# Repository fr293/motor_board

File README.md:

# stepper motor control board

This motor control board is designed to work with the [Open Flexure microscope](https://github.com/rwb27/openflexure_microscope) and connect to a Raspberry Pi.  It is based around three parallel ATTiny 841 microcontrollers running the Arduino Firmware through SpenceKonde's [ATTinyCore](https://github.com/SpenceKonde/ATTinyCore). 

Each ATTiny 841 controls a ULN2003 Darlington transistor array operating at 5V, running a 28BYJ-48 stepper motor with a 64:1 gear ratio.

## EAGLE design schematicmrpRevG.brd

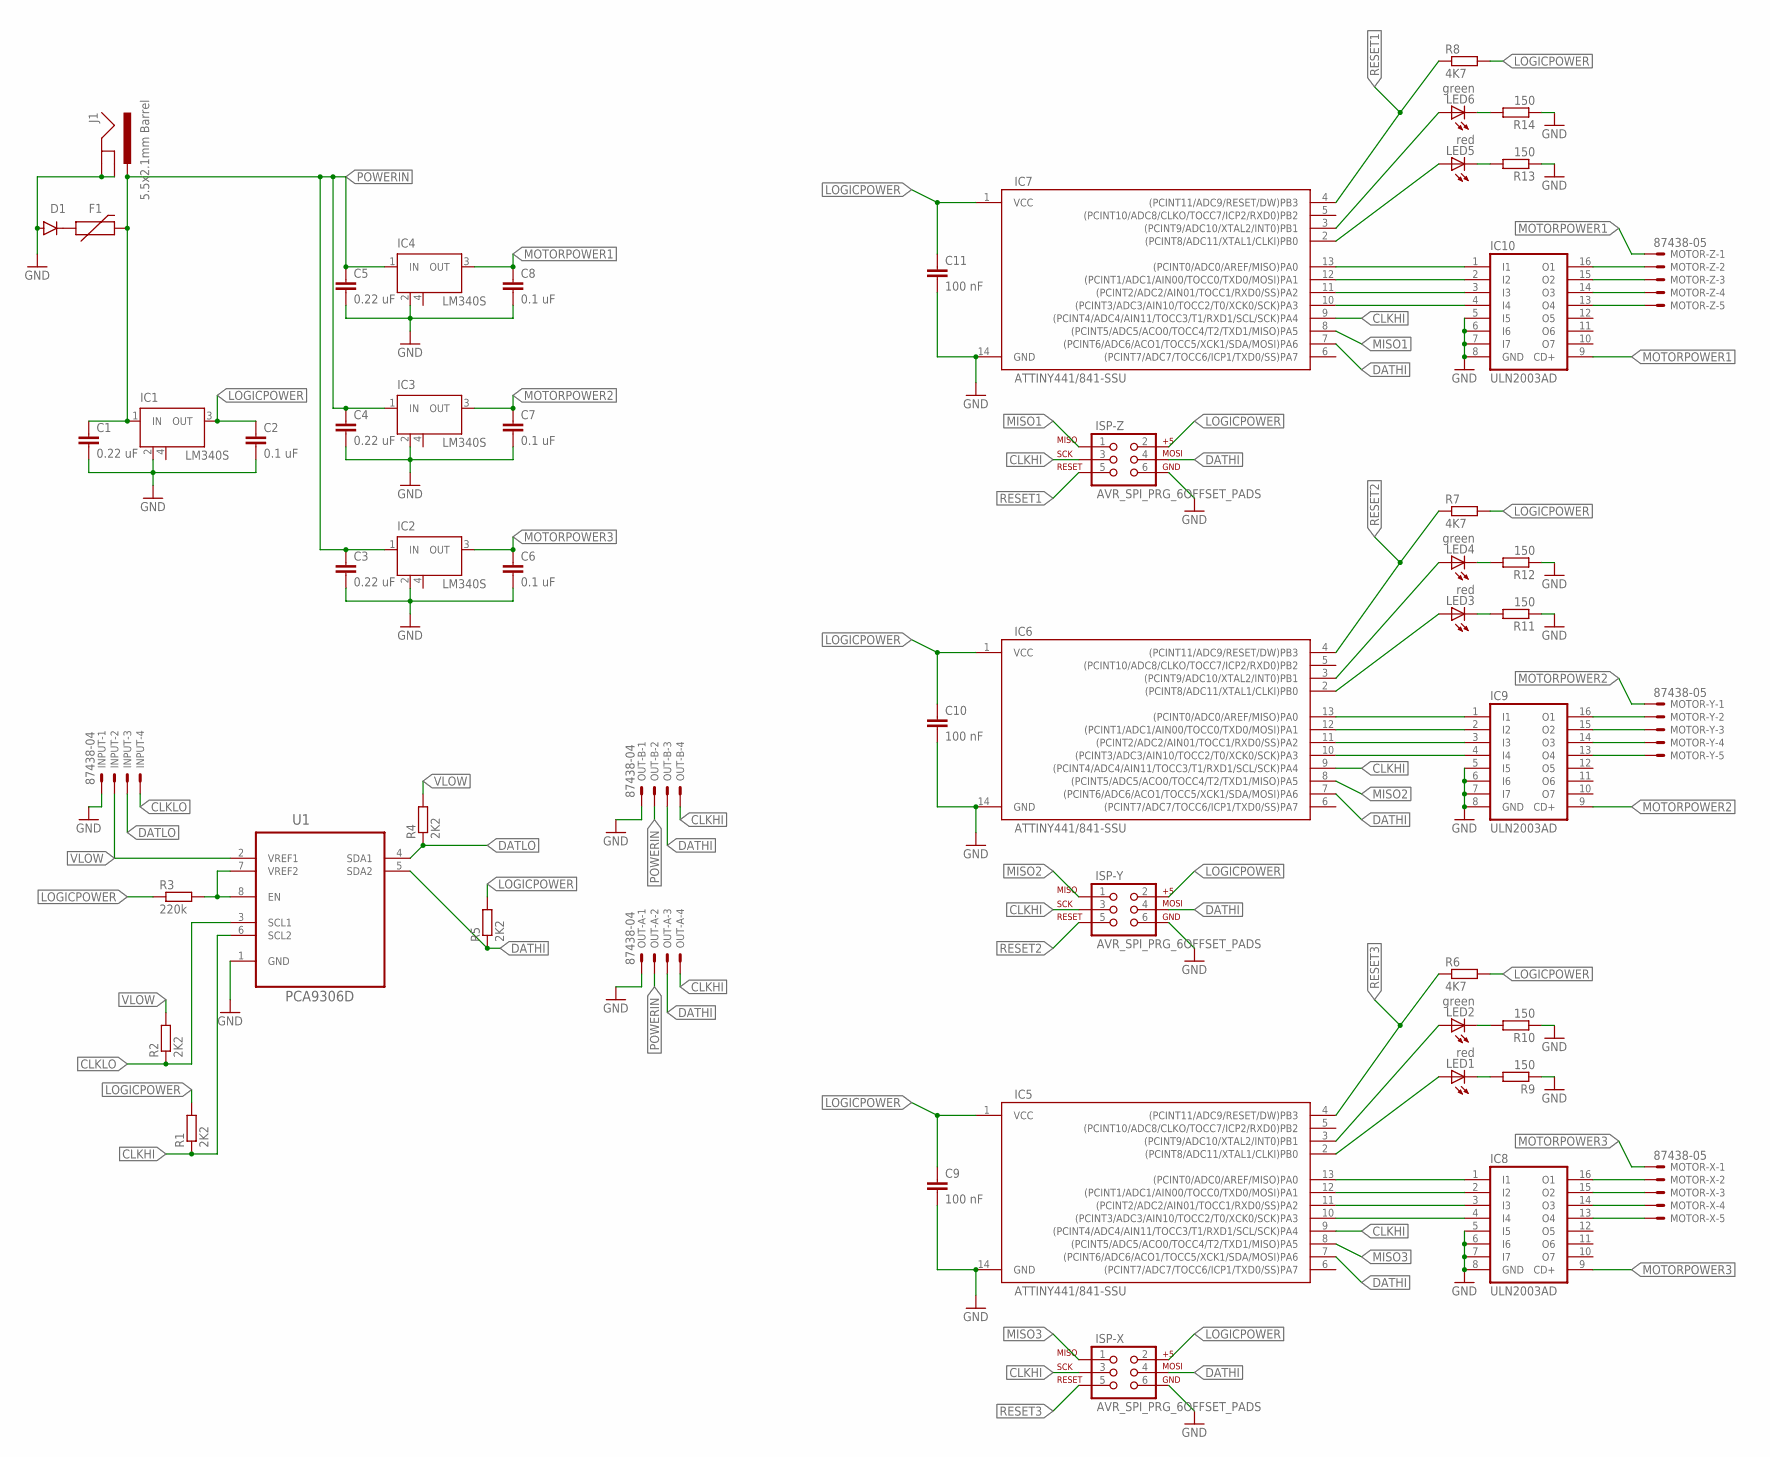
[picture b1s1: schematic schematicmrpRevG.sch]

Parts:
C1, C3, C4, C5: 0.22 uF; 0805; MPN 0805B224K500CT
C2, C6, C7, C8: 0.1 uF; 0805; MPN 08055C104KAT2A
C9, C10, C11: 100 nF; 0805; MPN 08055F104KAT2A
D1: 3A/600V; SMA-DIODE-KIT; MPN CD214A-B140LF
F1: PTCSMD; PTC-1206; MPN NANOSMDC012F-2
IC1, IC2, IC3, IC4: LM340S; SOT223; MPN LM340MP-5.0/NOPB
IC5, IC6, IC7: ATTINY441/841-SSU; SOIC14N; MPN ATTINY841-SSU
IC8, IC9, IC10: ULN2003AD; SO16; MPN ULN2003ADR
INPUT: 87438-04; MPN 87438-0443
ISP-X: AVR_SPI_PRG_6OFFSET_PADS; 2X3_OFFSET; MPN BG050-06A-0-0450-0737-0350-L-D
ISP-Y: AVR_SPI_PRG_6OFFSET_PADS; 2X3_OFFSET; MPN BG050-06A-0-0450-0737-0350-L-D
ISP-Z: AVR_SPI_PRG_6OFFSET_PADS; 2X3_OFFSET; MPN BG050-06A-0-0450-0737-0350-L-D
J1: 5.5x2.1mm Barrel; POWER_JACK_SMD; MPN FC68148S
LED1, LED3, LED5: red; CHIPLED_0805; MPN LSR976
LED2, LED4, LED6: green; CHIPLED_0805; MPN 5988170107F
MOTOR-X: 87438-05; MPN 87438-0543
MOTOR-Y: 87438-05; MPN 87438-0543
MOTOR-Z: 87438-05; MPN 87438-0543
OUT-A: 87438-04; MPN 87438-0443
OUT-B: 87438-04; MPN 87438-0443
R1, R2, R4, R5: 2K2; M0805; MPN ERA6AEB222V
R3: 220k; M0805; MPN WCR0805-220KFI
R6, R7, R8: 4K7; M0805; MPN WCR0805-4K7FI
R9, R10, R11, R12, R13, R14: 150; M0805; MPN WCR0805-150RFI
U1: PCA9306D; SOIC127P600X175-8N; MPN PCA9306D

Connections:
CLKHI: IC5.9 ((PCINT4/ADC4/AIN11/TOCC3/T1/RXD1/SCL/SC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), IC6.9 ((PCINT4/ADC4/AIN11/TOCC3/T1/RXD1/SCL/SC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), IC7.9 ((PCINT4/ADC4/AIN11/TOCC3/T1/RXD1/SCL/SC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), ISP-X.3, ISP-Y.3, ISP-Z.3, OUT-A.4, OUT-B.4, R1.1, U1.6 (SCL2)
CLKLO: INPUT.4, R2.1, U1.3 (SCL1)
DATHI: IC5.7 ((PCINT6/ADC6/ACO1/TOCC5/XCK1/SDA/MOSI)P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), IC6.7 ((PCINT6/ADC6/ACO1/TOCC5/XCK1/SDA/MOSI)P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), IC7.7 ((PCINT6/ADC6/ACO1/TOCC5/XCK1/SDA/MOSI)P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), ISP-X.4, ISP-Y.4, ISP-Z.4, OUT-A.3, OUT-B.3, R5.1, U1.5 (SDA2)
DATLO: INPUT.3, R4.1, U1.4 (SDA1)
GND: C1.2, C2.2, C3.2, C4.2, C5.2, C6.2, C7.2, C8.2, C9.2, C10.2, C11.2, D1.A, IC1.2 (GND), IC1.4 (GND), IC2.2 (GND), IC2.4 (GND), IC3.2 (GND), IC3.4 (GND), IC4.2 (GND), IC4.4 (GND), IC5.14 (GND), IC6.14 (GND), IC7.14 (GND), IC8.5 (I5), IC8.6 (I6), IC8.7 (I7), IC8.8 (GND), IC9.5 (I5), IC9.6 (I6), IC9.7 (I7), IC9.8 (GND), IC10.5 (I5), IC10.6 (I6), IC10.7 (I7), IC10.8 (GND), INPUT.1, ISP-X.6, ISP-Y.6, ISP-Z.6, J1.GND (GNDBREAK), J1.P$4 (GND), OUT-A.1, OUT-B.1, R9.1, R10.1, R11.1, R12.1, R13.1, R14.1, U1.1 (GND)
LOGICPOWER: C2.1, C9.1, C10.1, C11.1, IC1.3 (OUT), IC5.1 (VCC), IC6.1 (VCC), IC7.1 (VCC), ISP-X.2, ISP-Y.2, ISP-Z.2, R1.2, R3.1, R5.2, R6.2, R7.2, R8.2
MISO1: IC7.8 ((PCINT5/ADC5/ACO0/TOCC4/T2/TXD1/MISO)PA5), ISP-Z.1
MISO2: IC6.8 ((PCINT5/ADC5/ACO0/TOCC4/T2/TXD1/MISO)PA5), ISP-Y.1
MISO3: IC5.8 ((PCINT5/ADC5/ACO0/TOCC4/T2/TXD1/MISO)PA5), ISP-X.1
MOTORPOWER1: C8.1, IC4.3 (OUT), IC10.9 (CD+), MOTOR-Z.1
MOTORPOWER2: C7.1, IC3.3 (OUT), IC9.9 (CD+), MOTOR-Y.1
MOTORPOWER3: C6.1, IC2.3 (OUT), IC8.9 (CD+), MOTOR-X.1
unnamed: LED4.C, R12.2
unnamed: LED3.C, R11.2
unnamed: R3.2, U1.7 (VREF2), U1.8 (EN)
unnamed: IC10.16 (O1), MOTOR-Z.2
unnamed: IC10.15 (O2), MOTOR-Z.3
unnamed: LED6.C, R14.2
unnamed: LED5.C, R13.2
unnamed: IC10.14 (O3), MOTOR-Z.4
unnamed: IC10.13 (O4), MOTOR-Z.5
unnamed: IC7.13 ((PCINT0/ADC0/AREF/MISO)PA0), IC10.1 (I1)
unnamed: IC7.12 ((PCINT1/ADC1/AIN00/TOCC0/TXD0/MOSI)PA1), IC10.2 (I2)
unnamed: IC7.11 ((PCINT2/ADC2/AIN01/TOCC1/RXD0/SS)PA2), IC10.3 (I3)
unnamed: IC7.10 ((PCINT3/ADC3/AIN10/TOCC2/T0/XCK0/SCK)PA3), IC10.4 (I4)
unnamed: IC7.3 ((PCINT9/ADC10/XTAL2/INT0)PB1), LED6.A
unnamed: IC7.2 ((PCINT8/ADC11/XTAL1/CLKI)PB0), LED5.A
unnamed: IC9.16 (O1), MOTOR-Y.2
unnamed: IC9.15 (O2), MOTOR-Y.3
unnamed: IC9.14 (O3), MOTOR-Y.4
unnamed: IC9.13 (O4), MOTOR-Y.5
unnamed: IC6.13 ((PCINT0/ADC0/AREF/MISO)PA0), IC9.1 (I1)
unnamed: IC6.12 ((PCINT1/ADC1/AIN00/TOCC0/TXD0/MOSI)PA1), IC9.2 (I2)
unnamed: IC6.11 ((PCINT2/ADC2/AIN01/TOCC1/RXD0/SS)PA2), IC9.3 (I3)
unnamed: IC6.10 ((PCINT3/ADC3/AIN10/TOCC2/T0/XCK0/SCK)PA3), IC9.4 (I4)
unnamed: IC6.3 ((PCINT9/ADC10/XTAL2/INT0)PB1), LED4.A
unnamed: IC6.2 ((PCINT8/ADC11/XTAL1/CLKI)PB0), LED3.A
unnamed: LED2.C, R10.2
unnamed: LED1.C, R9.2
unnamed: IC8.16 (O1), MOTOR-X.2
unnamed: IC8.15 (O2), MOTOR-X.3
unnamed: IC8.14 (O3), MOTOR-X.4
unnamed: IC8.13 (O4), MOTOR-X.5
unnamed: IC5.13 ((PCINT0/ADC0/AREF/MISO)PA0), IC8.1 (I1)
unnamed: IC5.12 ((PCINT1/ADC1/AIN00/TOCC0/TXD0/MOSI)PA1), IC8.2 (I2)
unnamed: IC5.11 ((PCINT2/ADC2/AIN01/TOCC1/RXD0/SS)PA2), IC8.3 (I3)
unnamed: IC5.10 ((PCINT3/ADC3/AIN10/TOCC2/T0/XCK0/SCK)PA3), IC8.4 (I4)
unnamed: IC5.3 ((PCINT9/ADC10/XTAL2/INT0)PB1), LED2.A
unnamed: IC5.2 ((PCINT8/ADC11/XTAL1/CLKI)PB0), LED1.A
unnamed: D1.C, F1.1
POWERIN: C1.1, C3.1, C4.1, C5.1, F1.2, IC1.1 (IN), IC2.1 (IN), IC3.1 (IN), IC4.1 (IN), J1.VIN0 (PWR), OUT-A.2, OUT-B.2
RESET1: IC7.4 ((PCINT11/ADC9/RESET/DW)PB3), ISP-Z.5, R8.1
RESET2: IC6.4 ((PCINT11/ADC9/RESET/DW)PB3), ISP-Y.5, R7.1
RESET3: IC5.4 ((PCINT11/ADC9/RESET/DW)PB3), ISP-X.5, R6.1
VLOW: INPUT.2, R2.2, R4.2, U1.2 (VREF1)

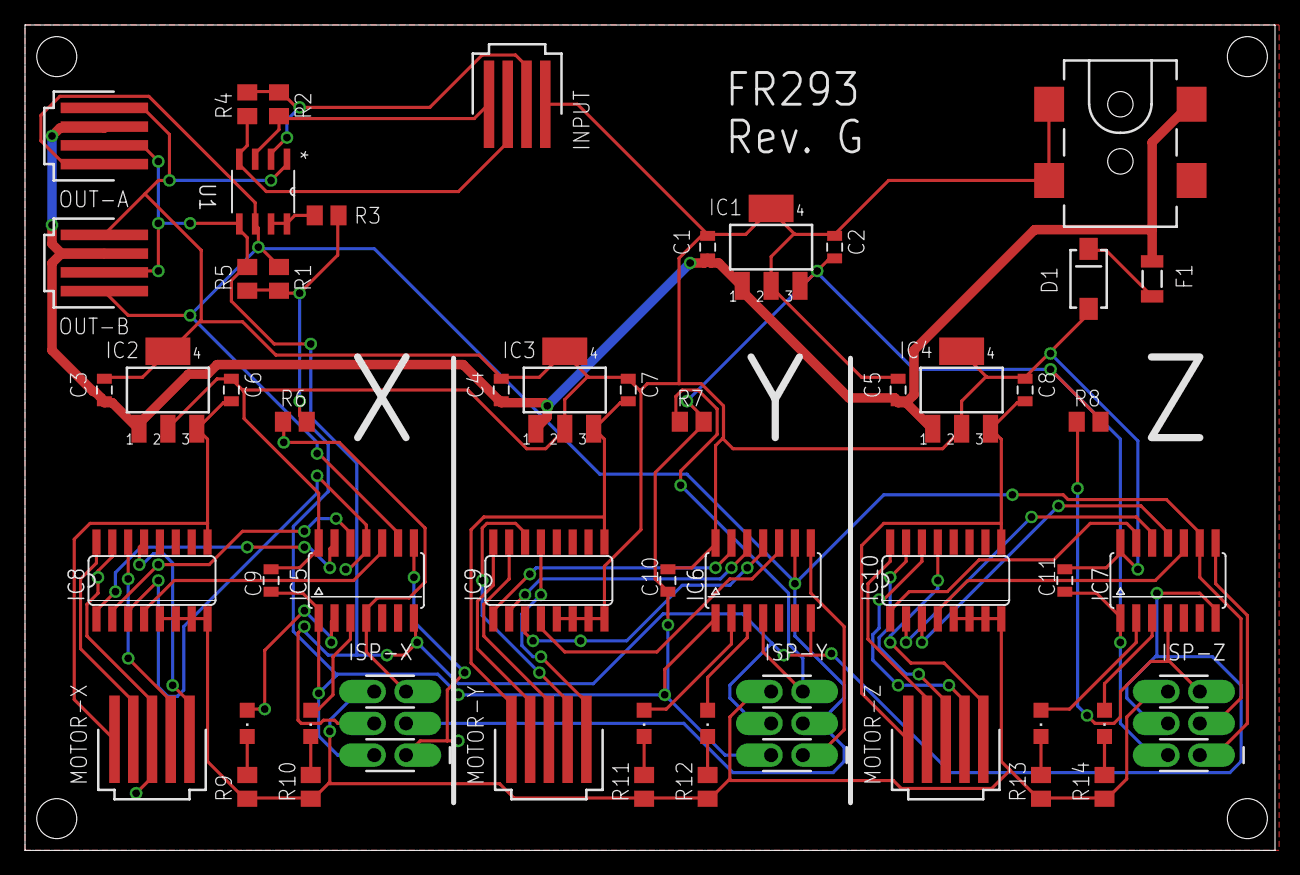
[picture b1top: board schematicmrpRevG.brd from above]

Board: 2 copper layers, 100.0 x 66.0 mm, 54 parts (0 on the bottom side), 55 nets.

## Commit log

2016-05-06 Added files via upload
2016-05-18 Add files via upload
    This model is a reasonably accurate upper bound on the 28BYJ-48 – 5V Stepper Motor
2016-10-18 Added bill of materials
    I went through the eagle files and made a bill of materials in an ODF
    spreadsheet. It has generic part specifications, footprints, and part
    numbers for the Digikey catalog.
2016-10-18 updated BOM
    resolved notes, updated parts quantities, confirmed ATTiny 841
2016-10-27 SMT stencils
    added board stencils for surface mount solder application
2016-10-31 Added info about the ATTinyCore in Readme
2016-11-02 added stencil DXF, fixed BSS138 digikey part X in BOM

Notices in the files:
parts and their libraries:
SparkFun-Capacitors: Licensing: Creative Commons ShareAlike 4.0 International - https://creativecommons.org/licenses/by-sa/4.0
